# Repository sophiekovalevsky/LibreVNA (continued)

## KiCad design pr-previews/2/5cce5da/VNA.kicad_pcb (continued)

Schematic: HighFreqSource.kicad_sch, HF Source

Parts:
C49, C53: 10uF; C_1206_3216Metric
C50, C52: 1uF; C_0603_1608Metric
C51: 10nF; C_0402_1005Metric
C54, C55, C56, C57, C61, C62, C64: 100nF; C_0402_1005Metric
C58, C59, C60: 1uF; C_0402_1005Metric
C63: 180pF; C_0402_1005Metric
C65, C68: 100nF/RF; C_0402_1005Metric
C66: 3n3F; C_0402_1005Metric
C67: 18pF; C_0402_1005Metric
C263, C264, C265, C266, C267, C268, C271, C272, C273, C274: 100pF; C_0402_1005Metric
IC8: AP2114H; SOT-223-3_TabPin2; MPN AP2114H-3.3TRG1
IC9: NCP702-3.3; SOT-23-5; MPN NCP702SN33T1G
IC10: MAX2871; QFN-32-1EP_5x5mm_P0.5mm_EP3.1x3.1mm; MPN MAX2871ETJ+
IC11, IC12: RFSW6042; QFN40P180X180X55-13T76N; MPN RFSW6042TR7
L19, L20, L64: FERRITE; R_0402_1005Metric; MPN BLM15AX601SN1
LP1: LP0603A-0947; FILTRDFN160X84X70-4N; MPN LP0603A0947ANTR
LP2: LP0603A-3500; FILTRDFN160X84X70-4N; MPN LP0603N3500ANTR
LP3: LP0603A-1880; FILTRDFN160X84X70-4N; MPN LP0603A1880ANTR
R10: 5.1k; R_0402_1005Metric
R11, R18, R19, R20, R21, R22, R23, R24, R25, R69, R163, R165: 10k; R_0402_1005Metric
R12, R13, R14: 49.9R; R_0402_1005Metric
R15: 1.8k; R_0402_1005Metric
R16: 82R; R_0402_1005Metric
R17: 330R; R_0402_1005Metric
R67, R68, R70, R164: 100R; R_0402_1005Metric
TP13, TP14: TestPoint; B1,27

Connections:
+3V3: L64.2; also elsewhere on the board
+5V/4: C49.1, C50.1, IC8.3 (VI), IC9.1 (IN), IC9.3 (EN); also elsewhere on the board
/HF Source/3V3_LDO2_SRC: C52.1, IC9.5 (OUT), L20.1
/HF Source/3V3_SRC_1: C56.1, C61.1, C64.1, IC10.16 (VCC_RF), IC10.17 (VCC_VCO), L19.2, R12.2, R13.2, TP14.1
/HF Source/3V3_SRC_2: C57.1, IC10.6 (VCC_CP), IC10.10 (VCC_PLL), IC11.3 (VDD), IC12.3 (VDD), L20.2, TP13.1
/HF Source/3V3_SRC_3: C54.1, C55.1, IC10.28 (VCC_DIG), IC10.32 (VDD_SD), L64.1
/HF Source/3v3_LDO1_SRC: C53.1, IC8.2 (VO), L19.1
/HF Source/FILT_IN_C1_R: IC11.2 (C1), R18.1, R21.1
/HF Source/FILT_IN_C2_R: IC11.1 (C2), R19.1, R20.1
/HF Source/FILT_OUT_C1_R: IC12.2 (C1), R24.1, R25.1
/HF Source/FILT_OUT_C2_R: IC12.1 (C2), R22.1, R23.1
/HF Source/SRC_BIAS_FILT: C60.1, IC10.23 (BIAS_FILT)
/HF Source/SRC_CE: C268.1, IC10.4 (CE), R163.1
/HF Source/SRC_CP_OUT: C63.1, C66.1, IC10.7 (CP_OUT), R15.1
/HF Source/SRC_DATA: IC10.2 (DATA), R67.1
/HF Source/SRC_FILT_IN_ANT: C65.2, IC11.7 (ANT)
/HF Source/SRC_FILT_IN_RF1: IC11.11 (RF2), LP1.4 (IN)
/HF Source/SRC_FILT_IN_RF3: IC11.6 (RF3), LP3.4 (IN)
/HF Source/SRC_FILT_IN_RF4: IC11.4 (RF4), LP2.4 (IN)
/HF Source/SRC_FILT_OUT_ANT: C68.1, IC12.7 (ANT)
/HF Source/SRC_FILT_OUT_RF1: IC12.9 (RF1), LP3.1 (OUT)
/HF Source/SRC_FILT_OUT_RF2: IC12.11 (RF2), LP2.1 (OUT)
/HF Source/SRC_FILT_OUT_RF4: IC12.4 (RF4), LP1.1 (OUT)
/HF Source/SRC_FILT_THRU: IC11.9 (RF1), IC12.6 (RF3)
/HF Source/SRC_LD: C274.1, IC10.25 (LD), R69.1
/HF Source/SRC_LE: IC10.3 (LE), R68.1
/HF Source/SRC_MUX: IC10.30 (MUX), R70.1
/HF Source/SRC_NOISE_FILT: C59.1, IC10.19 (NOISE_FILT)
/HF Source/SRC_REFOUT_EN: C272.1, IC10.26 (RFOUT_EN), R165.1
/HF Source/SRC_REF_IN: C51.2, IC10.29 (REF_IN)
/HF Source/SRC_REG: C58.1, IC10.24 (REG)
/HF Source/SRC_RFOUTA_N: C62.2, IC10.13 (RFOUTA_N), R13.1
/HF Source/SRC_RFOUTA_P: C65.1, IC10.12 (RFOUTA_P), R12.1
/HF Source/SRC_RSET: IC10.22 (RSET), R10.2
/HF Source/SRC_SCK: IC10.1 (CLK), R164.1
/HF Source/SRC_SW: IC10.5 (SW), R16.2, R17.1
/HF Source/SRC_TUNE: C67.2, IC10.20 (TUNE), R15.2
FILT_IN_C1: C263.1, R21.2; also elsewhere on the board
FILT_IN_C2: C264.1, R20.2; also elsewhere on the board
FILT_OUT_C1: C266.1, R24.2; also elsewhere on the board
FILT_OUT_C2: C265.1, R22.2; also elsewhere on the board
GND: C49.2, C50.2, C52.2, C53.2, C54.2, C55.2, C56.2, C57.2, C58.2, C59.2, C60.2, C61.2, C63.2, C64.2, C67.1, C263.2, C264.2, C265.2, C266.2, C267.2, C268.2, C271.2, C272.2, C273.2, C274.2, IC8.1 (GND), IC9.2 (GND), IC10.8 (GND_CP), IC10.9 (GND_PLL), IC10.11 (GND_RF), IC10.18 (GND_VCO), IC10.21 (GND_TUNE), IC10.27 (GND_DIG), IC10.31 (GND_SD), IC10.33 (EP), IC11.5 (GND), IC11.8 (GND), IC11.10 (GND), IC11.12 (GND), IC11.13 (GND), IC12.5 (GND), IC12.8 (GND), IC12.10 (GND), IC12.12 (GND), IC12.13 (GND), LP1.2 (GND), LP1.3 (GND), LP2.2 (GND), LP2.3 (GND), LP3.2 (GND), LP3.3 (GND), R10.1, R11.1, R14.1, R17.2, R18.2, R19.2, R23.2, R25.2; also elsewhere on the board
unnamed: C62.1, R14.2
unnamed: C66.2, R16.1
SOURCE_CE: C267.1, R11.2, R163.2; also elsewhere on the board
SOURCE_CLK: R164.2; also elsewhere on the board
SOURCE_HIGHBAND: C68.2; also elsewhere on the board
SOURCE_LD: C273.1, R69.2; also elsewhere on the board
SOURCE_LE: R68.2; also elsewhere on the board
SOURCE_MOSI: R67.2; also elsewhere on the board
SOURCE_MUX: R70.2; also elsewhere on the board
SOURCE_REF: C51.1; also elsewhere on the board
SOURCE_RF_EN: C271.1, R165.2; also elsewhere on the board

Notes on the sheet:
C1/C2 should not be driven above 1.8V
All I/O using 3V3 levels
3x 3V3
up to 200mA current consumption
ca. 2dbm
ca. -1db
5dbm
Approx. 450kHz loop bandwidth

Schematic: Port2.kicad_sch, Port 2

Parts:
C133, C136, C146, C147: 100nF/RF; C_0402_1005Metric
C134, C135, C139, C140, C151, C152, C153, C154, C155, C156, C159, C169: 100nF; C_0402_1005Metric
C137, C138, C145, C166, C168: 1uF; C_0402_1005Metric
C141, C142, C143, C148, C157, C160: 10nF; C_0402_1005Metric
C144, C149, C150: DNP; C_0402_1005Metric; not fitted
C158, C162, C163, C164: 330pF; C_0402_1005Metric
C161: 120pF; C_0402_1005Metric
C165: 150pF; C_0402_1005Metric
C167: 33pF; C_0402_1005Metric
IC27: LT5560; WSON-8-1EP_3x3mm_P0.5mm_EP1.45x2.4mm; MPN LT5560EDD
IC28: THS4521IDGKR; VSSOP-8_3.0x3.0mm_P0.65mm; MPN THS4521IDGKR
IC29: ADL5801; QFN-24-1EP_4x4mm_P0.5mm_EP2.6x2.6mm; MPN ADL5801
IC30: NCP702-1.8; SOT-23-5; MPN NCP702SN18T1G
IC31: MCP33131D-10-E/MS; VSSOP-10_3x3mm_P0.5mm; MPN MCP33131D-10-E/MS
J3: SMA; BU-1420701851; MPN AMPHENOL-132289
L38, L39, L40, L41: 330nH; L_0402_1005Metric; MPN LQW15CNR33J10D
L42, L43: 68nH; L_0402_1005Metric; MPN LQW15AN68NJ00D
L44, L45: 33nH; L_0402_1005Metric; MPN LQW15AN33NJ00D
L54, L55, L56, L57, L58: FERRITE; R_0402_1005Metric; MPN BLM15AX601SN1
R40: PAT0816-C-3DB-T5; PAT0816
R47: PAT0816-C-3DB-T5; PAT0816; not fitted
R72, R73, R76: 49.9R; R_0402_1005Metric
R80, R81, R85, R86, R88, R89: 220R; R_0402_1005Metric
R82, R83: 6.8k; R_0402_1005Metric
R84: DNP; R_0402_1005Metric; not fitted
R87: 1k; R_0402_1005Metric
R90, R93: 56R; R_0402_1005Metric
R91, R92: 20R; R_0402_1005Metric
T2: B012-617DB-1-63-B331; EASTEVER_BALUN; MPN B012-617DB-1-63-B331
TP18: TestPoint; B1,27

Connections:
+3V3: C169.2, IC31.9 (SDI), IC31.10 (DVIO); also elsewhere on the board
+5V/2: L54.2, L55.2, L56.2, L57.2, L58.2, R87.1; also elsewhere on the board
GND: C134.1, C139.1, C140.1, C141.2, C142.2, C143.2, C145.2, C148.2, C152.1, C153.2, C154.2, C155.1, C156.2, C159.2, C162.1, C164.2, C166.2, C168.2, C169.1, IC27.9 (PGND), IC28.6 (V_{S-}), IC29.1 (GND), IC29.2 (GND), IC29.5 (GND), IC29.6 (GND), IC29.8 (GND), IC29.12 (GND), IC29.14 (GND), IC29.17 (GND), IC29.19 (GND), IC29.23 (GND), IC29.25 (GND), IC30.2 (GND), IC31.5 (GND), J3.G@1 (2), J3.G@2 (2), J3.G@3 (2), J3.G@4 (2), L38.2, L39.2, R40.3, R47.3, R76.2; also elsewhere on the board
unnamed: C133.2, R40.2
unnamed: C136.1, J3.1
unnamed: C149.2, IC28.5, R82.2, R85.2
unnamed: C150.1, IC28.4, R83.1, R86.2
unnamed: C156.1, C159.1, L40.1, L41.1, L55.1
unnamed: C157.2, C161.1, L42.1
unnamed: C158.1, R85.1, R88.2
unnamed: C158.2, R86.1, R89.2
unnamed: C160.2, C161.2, L43.1
unnamed: C165.1, L42.2, L44.1
unnamed: C165.2, L43.2, L45.1
unnamed: C167.1, L44.2, R90.2, R91.2
unnamed: C167.2, L45.2, R90.1, R92.2
unnamed: IC27.3 (IN+), L38.1, R92.1, R93.2
unnamed: IC27.4 (IN-), L39.1, R91.1, R93.1
unnamed: C135.2, IC27.8 (LO+)
unnamed: C134.2, IC27.1 (LO-)
unnamed: C137.1, IC27.6 (OUT+), R80.2
unnamed: C138.1, IC27.5 (OUT-), R81.2
unnamed: C139.2, C140.2, IC27.7 (VCC), L57.1, R80.1, R81.1
unnamed: C137.2, C149.1, IC28.8 (+), R82.1
unnamed: C138.2, C150.2, IC28.1 (-), R83.2
unnamed: C153.1, IC28.2 (V_{OCM})
unnamed: C152.2, IC28.3 (V_{S+}), L56.1
unnamed: IC29.11 (DETO), R84.2
unnamed: C146.2, IC29.15 (IN+)
unnamed: C147.2, IC29.16 (IN-)
unnamed: C151.2, IC29.3 (LO+)
unnamed: C154.1, IC29.4 (LO-)
unnamed: C157.1, IC29.20 (OUT+), L40.2
unnamed: C160.1, IC29.21 (OUT-), L41.2
unnamed: C141.1, C142.1, C143.1, C145.1, C148.1, IC29.7 (VPLO), IC29.13 (VPDT), IC29.18 (VPRF), IC29.24 (VPLO), L54.1
unnamed: C155.2, IC29.10 (VSET), R84.1, R87.2
unnamed: C166.1, IC30.1 (IN), IC30.3 (EN), IC31.1 (VREF), L58.1
unnamed: C168.1, IC30.5 (OUT), IC31.2 (AVDD), TP18.1
unnamed: C162.2, C163.1, IC31.3 (AIN+), R88.1
unnamed: C163.2, C164.1, IC31.4 (AIN-), R89.1
unnamed: R40.1, R72.2, R73.2
unnamed: C144.1, C147.1, T2.3 (IN+)
unnamed: C144.2, C146.1, T2.2 (IN-)
unnamed: C136.2, R47.1, R47.2, R72.1, T2.4 (OUT+)
unnamed: R73.1, R76.1, T2.6 (OUT-)
PORT2LO1: C151.1; also elsewhere on the board
PORT2LO2: C135.1; also elsewhere on the board
PORT2MIX1_EN: IC29.9 (ENBL); also elsewhere on the board
PORT2MIX2_EN: IC27.2 (EN), IC28.7 (~PD); also elsewhere on the board
PORT2SRC: C133.1; also elsewhere on the board
PORT2_CONVSTART: IC31.6 (CONVST); also elsewhere on the board
PORT2_SCLK: IC31.8 (SCLK); also elsewhere on the board
PORT2_SDO: IC31.7 (SDO); also elsewhere on the board

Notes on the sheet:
1MS/s ADC
-10db pad
Downconverter to 1.IF (ca. 60MHz)
Return loss bridge
-3db pad
60MHz lowpass and conversion from 250 Ohm to 28 Ohm impedance
300kHz lowpass
Final IF amplifier and ADC driver
P1db: 0dbm
(28 Ohm impedance)
Downconverter to 1.IF (ca. 250kHz)
Cut wire if attenuator placed

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
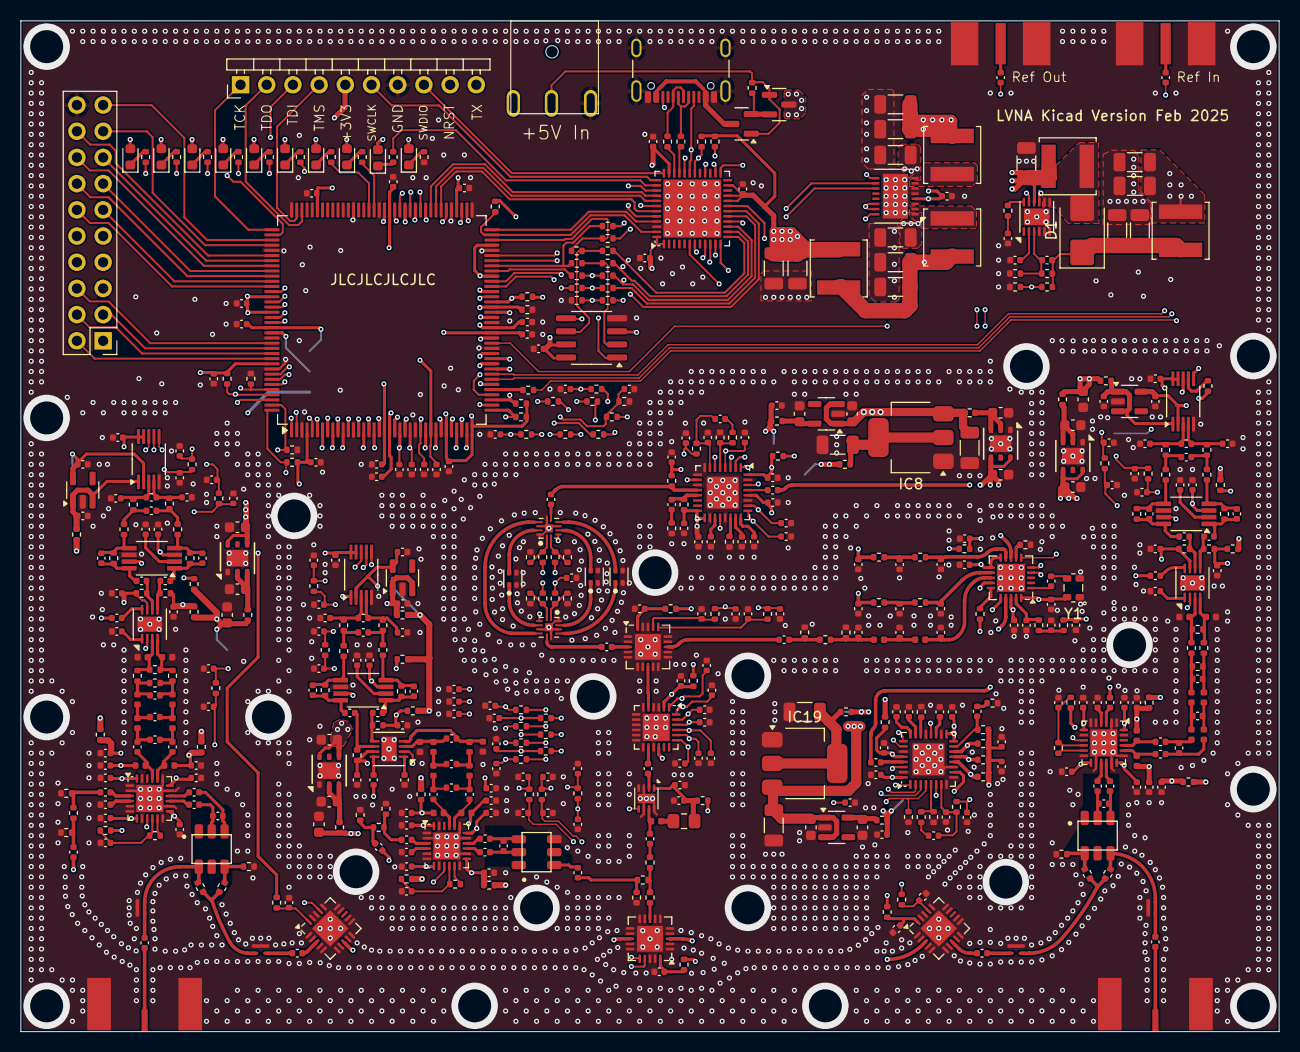
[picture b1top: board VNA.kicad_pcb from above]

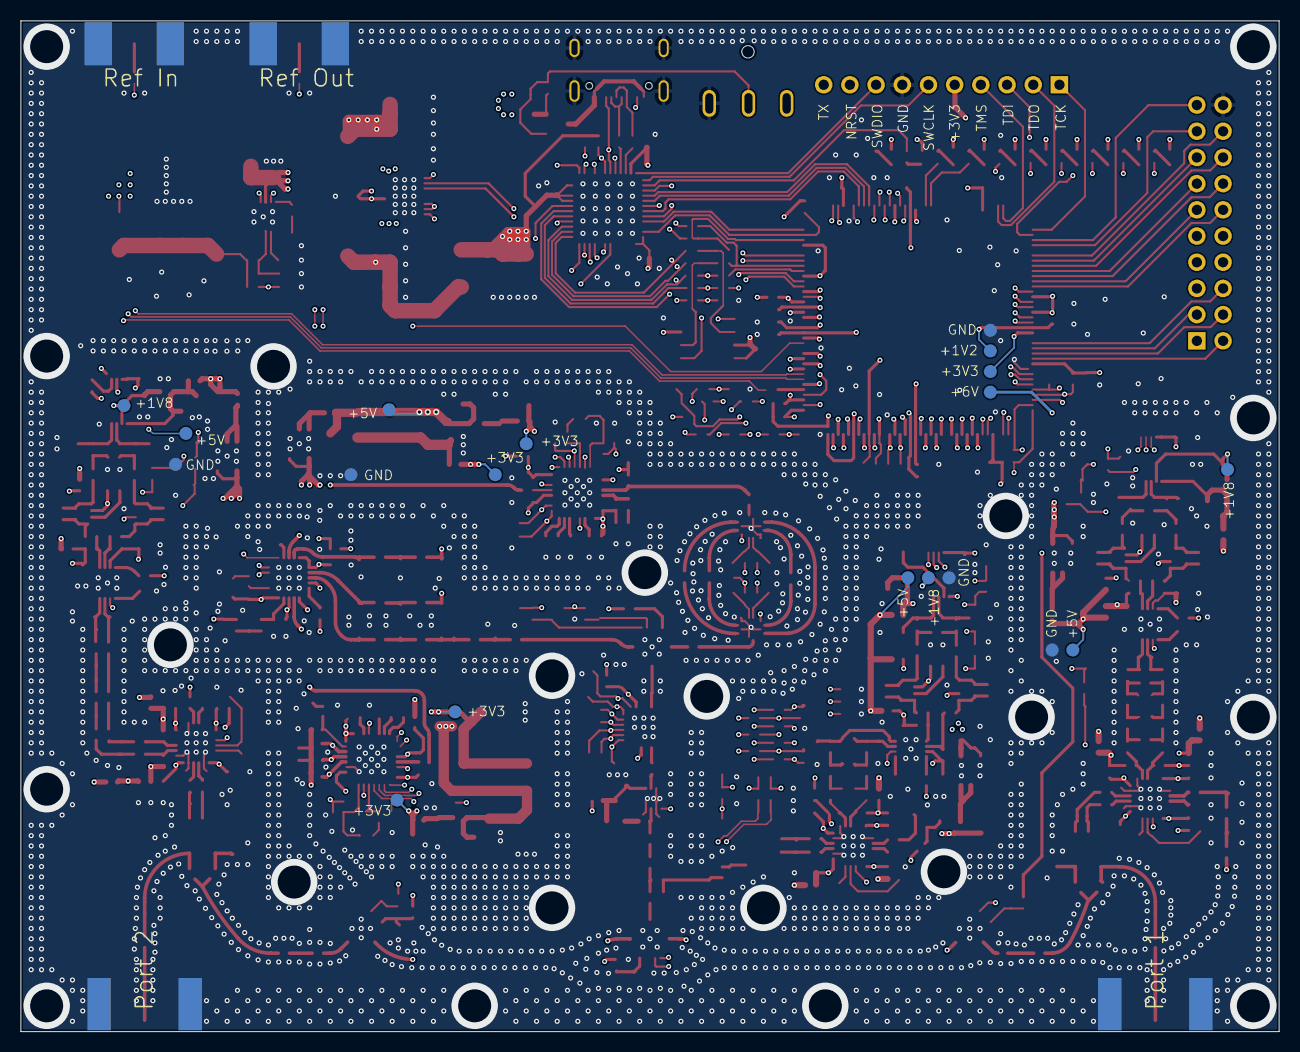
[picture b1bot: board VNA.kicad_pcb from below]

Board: 6 copper layers, 122.0 x 98.0 mm, 592 parts (20 on the bottom side), 402 nets.

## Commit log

2021-07-05 actions: include version
2021-07-05 actions: update release
2025-08-09 CI(kicad): use kiri
2025-08-09 some tests
2025-08-09 Update Kiri output for PR #2
